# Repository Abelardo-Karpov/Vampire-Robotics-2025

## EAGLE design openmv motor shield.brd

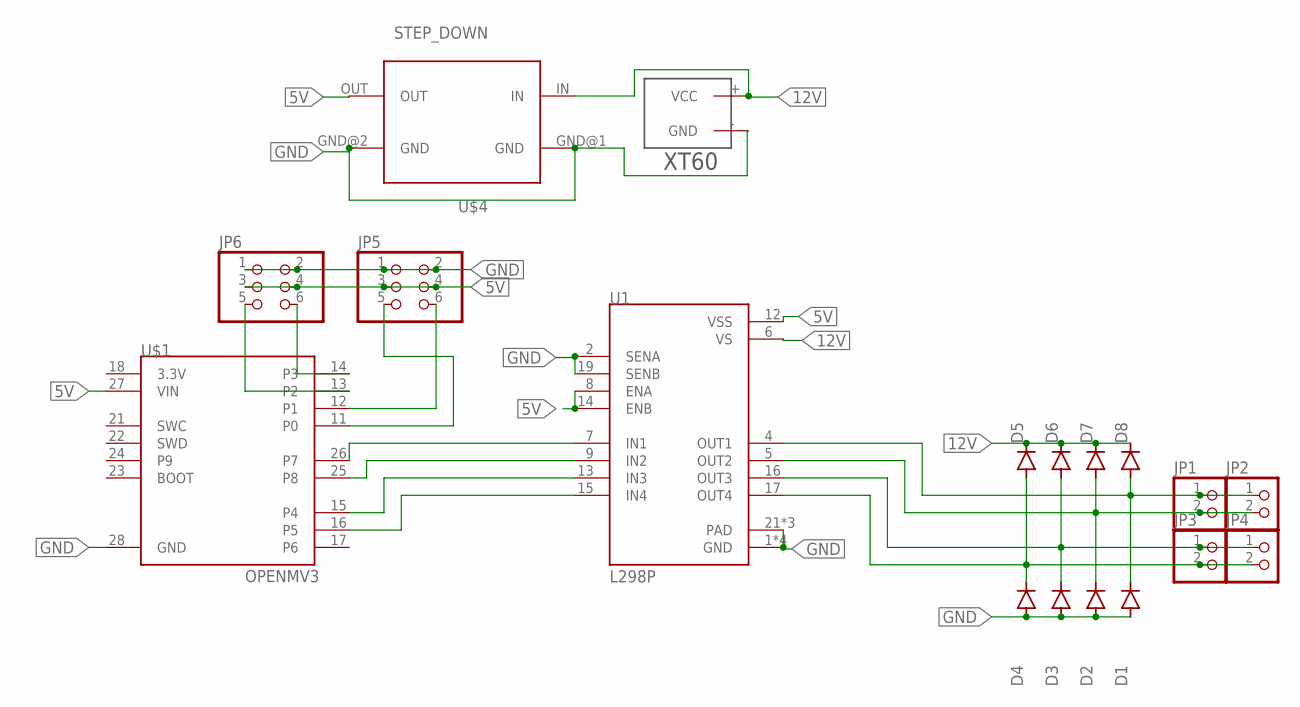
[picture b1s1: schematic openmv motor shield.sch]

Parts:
D1, D2, D3, D4, D5, D6, D7, D8: SRP100; DO41-10
JP1, JP2, JP3, JP4: PINHD-1X2; 1X02
JP5, JP6: PINHD-2X3; 2X03
U1: L298P; SOIC127P1420X360-20N
U$1: OPENMV3
U$2: XT60
U$4: STEP_DOWN; STEP_DOWN_5V

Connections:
5V: JP5.3, JP5.4, JP6.3, JP6.4, U1.8 (ENA), U1.12 (VSS), U1.14 (ENB), U$1.27 (VIN), U$4.OUT
12V: D5.C, D6.C, D7.C, D8.C, U1.6 (VS), U$2.+ (VCC), U$4.IN
GND: D1.A, D2.A, D3.A, D4.A, JP5.1, JP5.2, JP6.1, JP6.2, U1.1 (GND), U1.2 (SENA), U1.10 (GND), U1.11 (GND), U1.19 (SENB), U1.20 (GND), U1.21 (PAD), U1.22 (PAD), U1.23 (PAD), U$1.28 (GND), U$2.- (GND), U$4.GND@1 (GND), U$4.GND@2 (GND)
unnamed: D4.C, D5.A, JP3.2, JP4.2, U1.17 (OUT4)
unnamed: JP5.5, U$1.11 (P0)
unnamed: D3.C, D6.A, JP3.1, JP4.1, U1.16 (OUT3)
unnamed: D2.C, D7.A, JP1.2, JP2.2, U1.5 (OUT2)
unnamed: D1.C, D8.A, JP1.1, JP2.1, U1.4 (OUT1)
unnamed: U1.7 (IN1), U$1.26 (P7)
unnamed: U1.9 (IN2), U$1.25 (P8)
unnamed: U1.13 (IN3), U$1.15 (P4)
unnamed: U1.15 (IN4), U$1.16 (P5)
unnamed: JP5.6, U$1.12 (P1)
unnamed: JP6.5, U$1.13 (P2)
unnamed: JP6.6, U$1.14 (P3)

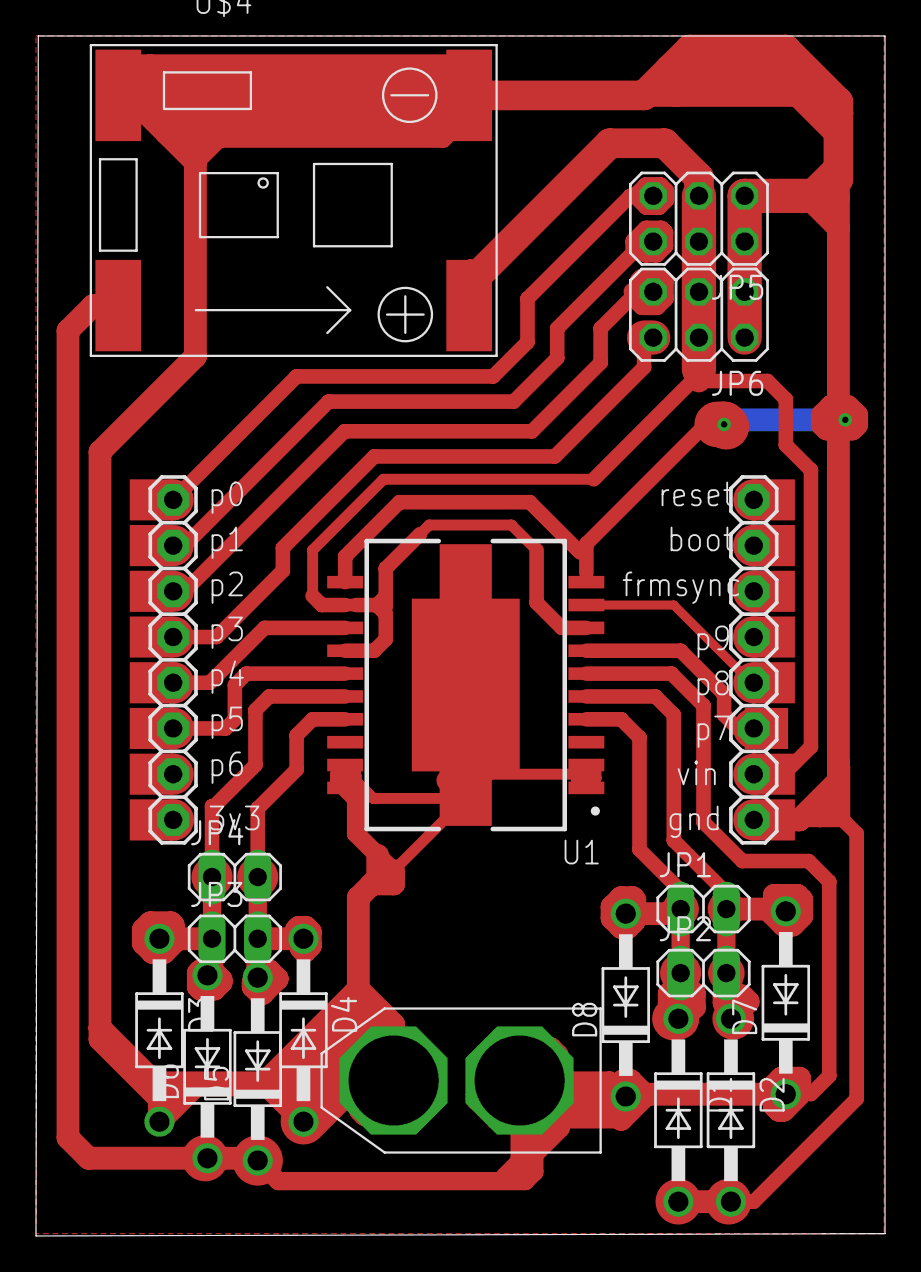
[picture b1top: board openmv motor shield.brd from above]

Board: 2 copper layers, 47.2 x 66.7 mm, 18 parts (0 on the bottom side), 15 nets.
